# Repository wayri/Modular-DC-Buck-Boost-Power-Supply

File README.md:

# Programmable Power-Supply

The goal of this project is to design and develop a DC-DC buck-boost programmable power supply which has CC CV and programmable voltage modes

This repository include/will include, schematics, assembly instructions, design, related calculations, and code to make the supply work.

## Current Progress:

- Discreet stage : The supply is currently implemented as a buck boost regulator with CC CV capabilities entirely using discreet ICs like basic logic gates and oscillators like NE555 (See picture above)

- Embedded Stage : This stage will completely digitize the control and also provide programmable capability along with support hardware.

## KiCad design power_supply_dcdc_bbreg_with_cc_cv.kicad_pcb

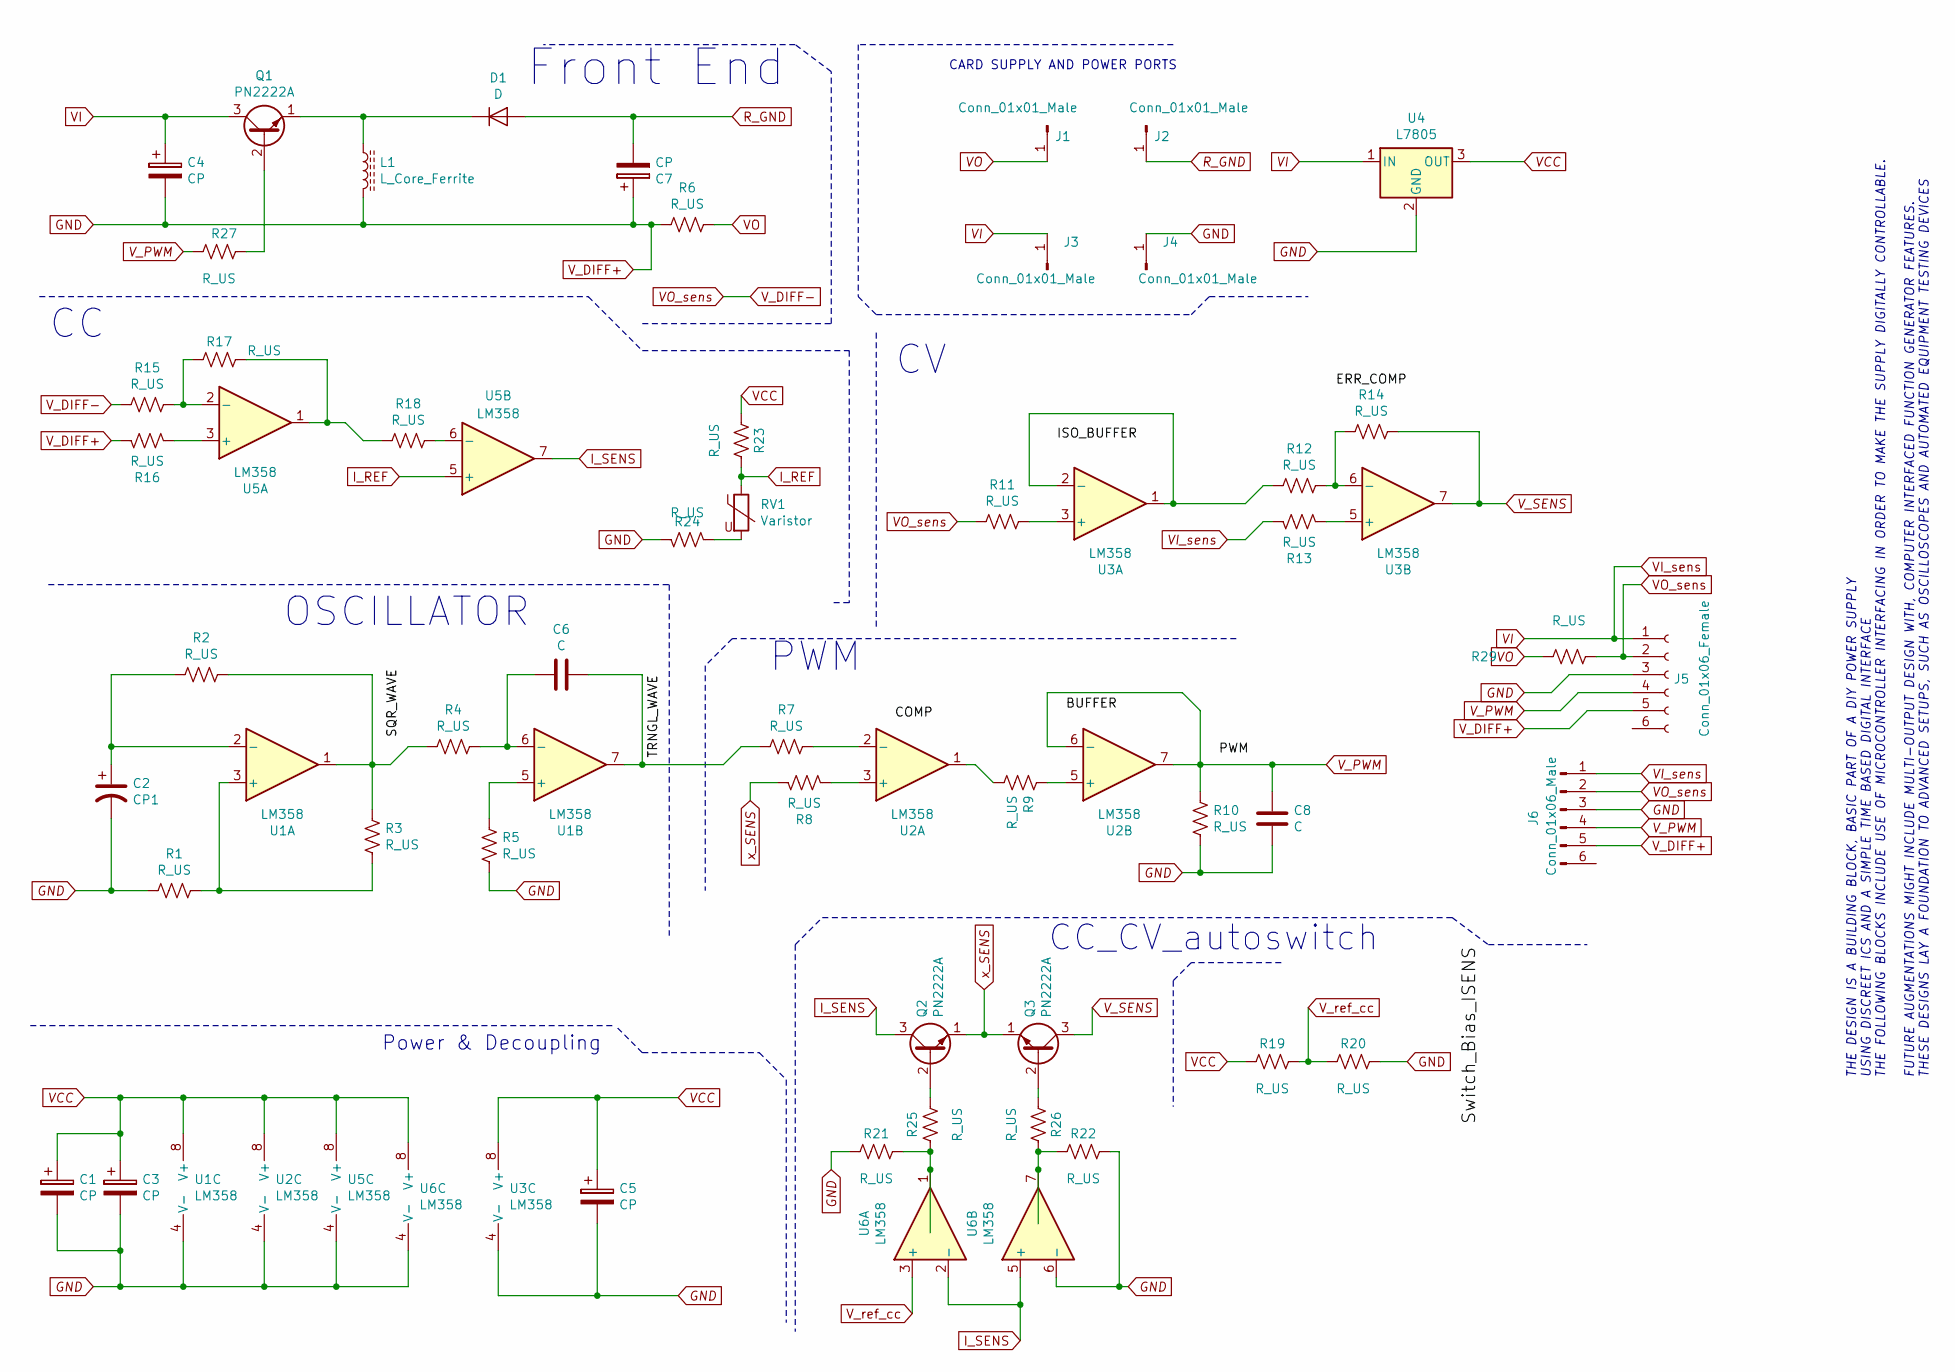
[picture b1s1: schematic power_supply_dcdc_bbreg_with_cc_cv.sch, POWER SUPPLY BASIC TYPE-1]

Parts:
C1, C3, C5: CP; C_1206_3216Metric
C2: CP1; CP_Radial_D8.0mm_P5.00mm
C4, C7: CP; CP_Radial_D13.0mm_P7.50mm
C6, C8: C; C_1206_3216Metric
D1: D; D_5KPW_P12.70mm_Horizontal
J1, J2, J3, J4: Conn_01x01_Male; PinHeader_1x01_P2.54mm_Vertical
J5: Conn_01x06_Female; PinSocket_1x06_P2.00mm_Vertical
J6: Conn_01x06_Male; PinHeader_1x06_P2.00mm_Vertical
L1: L_Core_Ferrite; L_Radial_D18.0mm_P10.00mm
Q1: PN2222A; TO-92
Q2, Q3: PN2222A; TO-92_Inline
R1, R2, R3, R4, R5, R7, R8, R9, R10, R11, R12, R13, R14, R15, R16, R17, R18, R19, R20, R21, R22, R23, R24, R25, R26, R27, R29: R_US; R_0603_1608Metric
R6: R_US; R_1206_3216Metric
RV1: Varistor; RV_Disc_D9mm_W4mm_P5mm
U1, U2, U3, U5, U6: LM358; DIP-8_W7.62mm
U4: L7805; TO-220-3_Horizontal_TabDown

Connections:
GND: C1.2, C2.2, C3.2, C4.2, C5.2, C7.1, C8.2, J4.1, J5.3, J5.5, J6.3, J6.5, L1.2, R1.2, R5.2, R6.2, R10.1, R16.2, R20.1, R21.2, R22.1, R24.1, U1.4 (V-), U2.4 (V-), U3.4 (V-), U4.2 (GND), U5.4 (V-), U6.4 (V-), U6.6 (-)
I_REF: R23.1, RV1.1, U5.5 (+)
I_SENS: Q2.3 (C), U5.7, U6.2 (-), U6.5 (+)
unnamed: C2.1, R2.2, U1.2 (-)
unnamed: C6.1, R7.2, U1.7
unnamed: C6.2, R4.2, U1.6 (-)
unnamed: D1.1 (K), L1.1, Q1.1 (E)
unnamed: Q1.2 (B), R27.2
unnamed: Q2.2 (B), R25.1
unnamed: Q3.2 (B), R26.2
unnamed: R1.1, R3.1, U1.3 (+)
unnamed: R2.1, R3.2, R4.1, U1.1
unnamed: R5.1, U1.5 (+)
unnamed: R7.1, U2.2 (-)
unnamed: R8.1, U2.3 (+)
unnamed: R9.1, U2.1
unnamed: R9.2, U2.5 (+)
unnamed: R11.2, U3.3 (+)
unnamed: R12.1, U3.1, U3.2 (-)
unnamed: R12.2, R14.1, U3.6 (-)
unnamed: R13.2, U3.5 (+)
unnamed: R15.1, R17.2, U5.2 (-)
unnamed: R16.1, U5.3 (+)
unnamed: R17.1, R18.2, U5.1
unnamed: R18.1, U5.6 (-)
unnamed: R21.1, R25.2, U6.1
unnamed: R22.2, R26.1, U6.7
unnamed: R24.2, RV1.2
R_GND: C7.2, D1.2 (A), J2.1
VCC: C1.1, C3.1, C5.1, R19.2, R23.2, U1.8 (V+), U2.8 (V+), U3.8 (V+), U4.3 (OUT), U5.8 (V+), U6.8 (V+)
VI: C4.1, J3.1, J5.1, J6.1, Q1.3 (C), R13.1, U4.1 (IN)
VO: J1.1, R6.1, R29.1
VO_sens: J5.2, J6.2, R11.1, R15.2, R29.2
V_PWM: C8.1, J5.4, J6.4, R10.2, R27.1, U2.6 (-), U2.7
V_SENS: Q3.3 (C), R14.2, U3.7
V_ref_cc: R19.1, R20.2, U6.3 (+)
x_SENS: Q2.1 (E), Q3.1 (E), R8.2

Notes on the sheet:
THE DESIGN IS A BUILDING BLOCK, BASIC PART OF A DIY POWER SUPPLY USING DISCREET ICS AND A SIMPLE TIME BASED DIGITAL INTERFACE THE FOLLOWING BLOCKS INCLUDE USE OF MICROCONTROLLER INTERFACING IN ORDER TO MAKE THE SUPPLY DIGITALLY CONTROLLABLE. FUTURE AUGMENTATIONS MIGHT INCLUDE MULTI-OUTPUT DESIGN WI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
Front End
Power & Decoupling
CARD SUPPLY AND POWER PORTS
OSCILLATOR
PWM
CC_CV_autoswitch

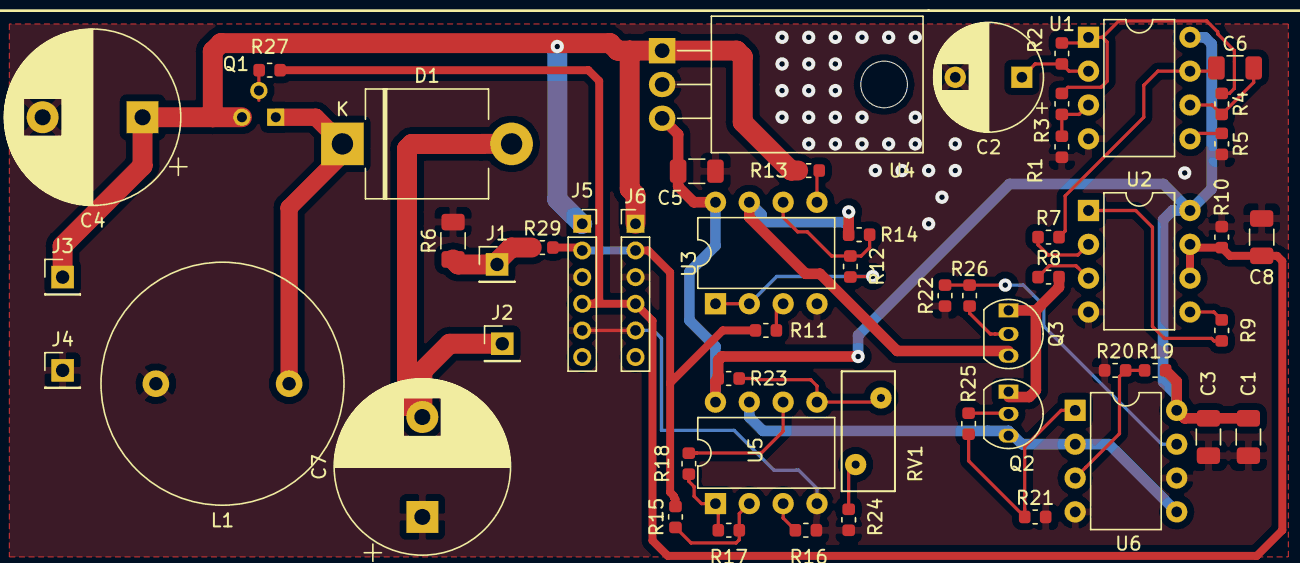
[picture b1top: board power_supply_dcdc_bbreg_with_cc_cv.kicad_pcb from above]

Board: 2 copper layers, 54 parts (1 on the bottom side), 37 nets.

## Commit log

2019-05-25 added design files
